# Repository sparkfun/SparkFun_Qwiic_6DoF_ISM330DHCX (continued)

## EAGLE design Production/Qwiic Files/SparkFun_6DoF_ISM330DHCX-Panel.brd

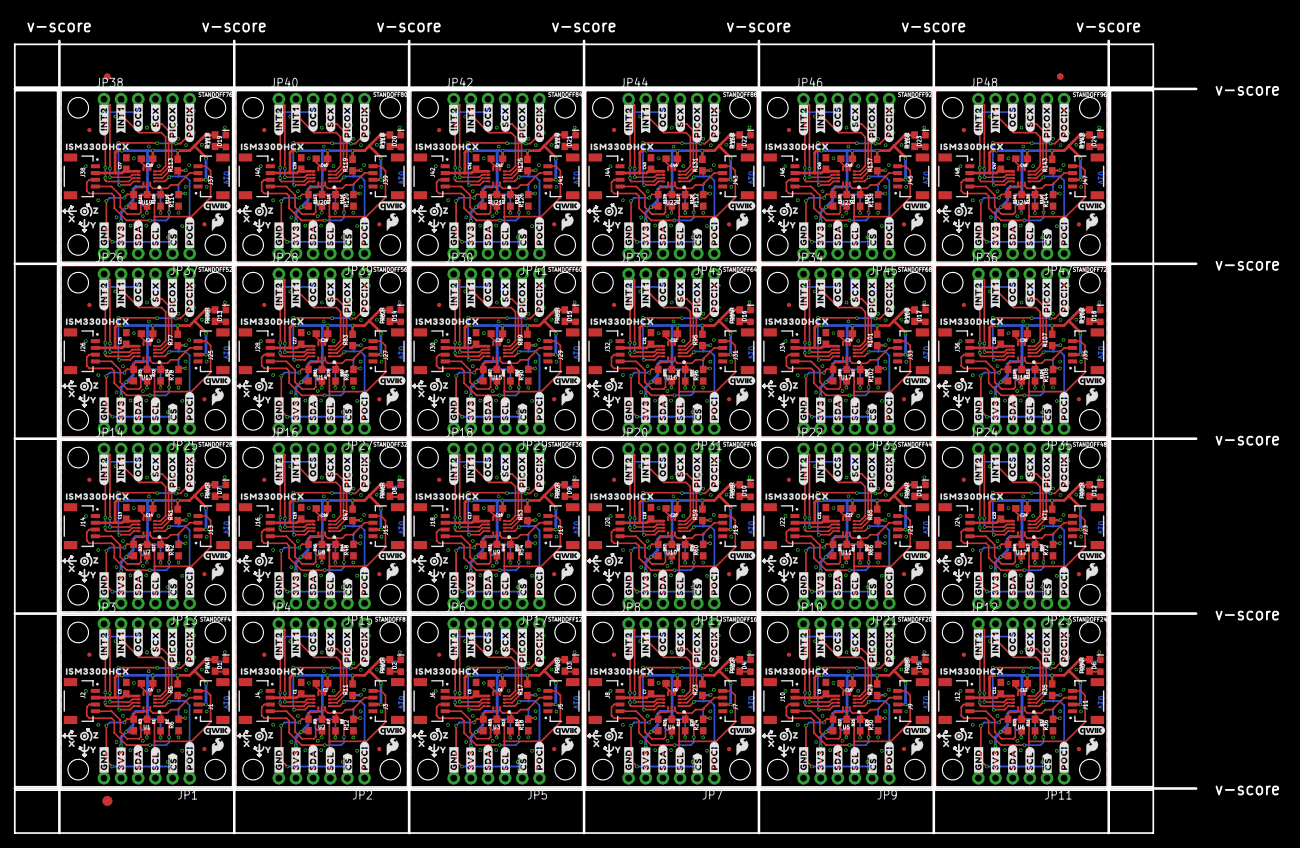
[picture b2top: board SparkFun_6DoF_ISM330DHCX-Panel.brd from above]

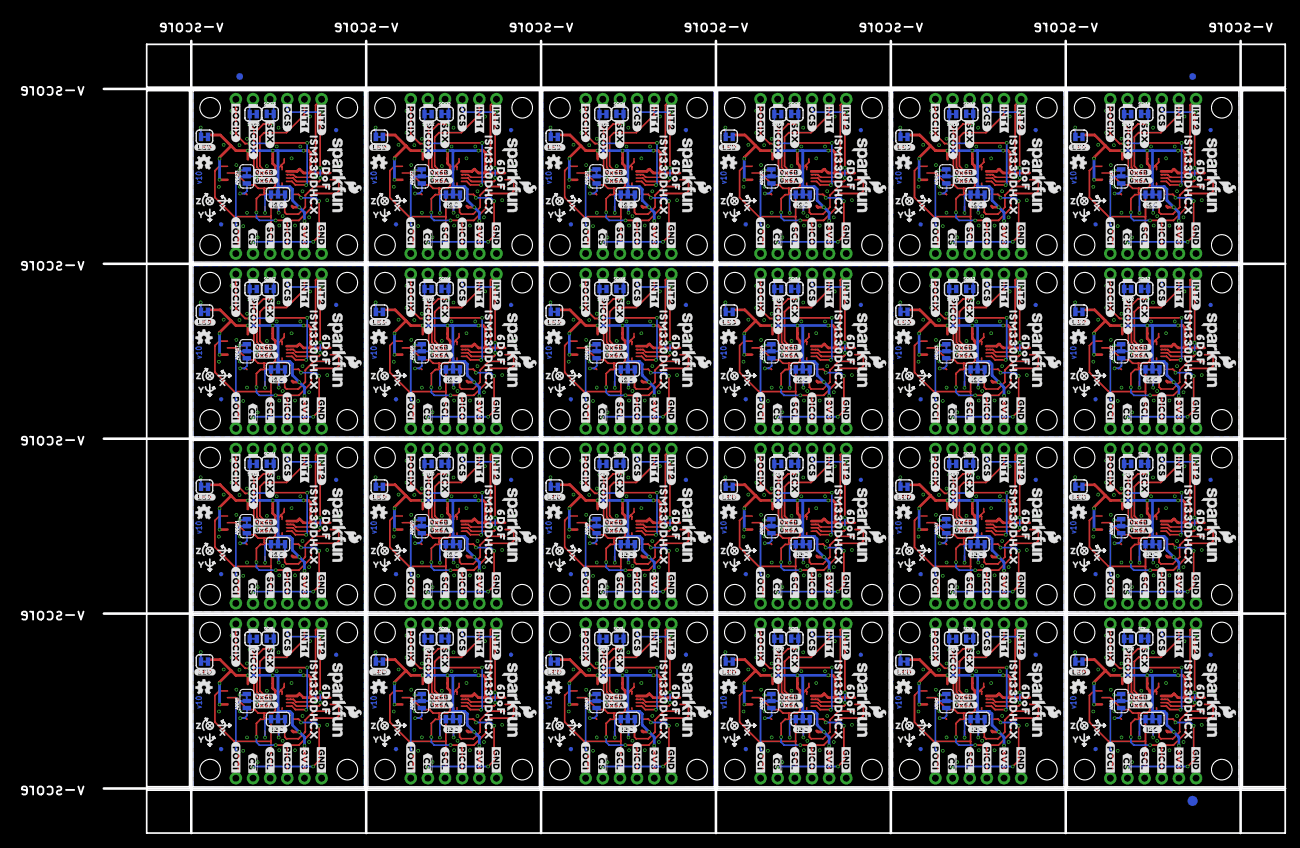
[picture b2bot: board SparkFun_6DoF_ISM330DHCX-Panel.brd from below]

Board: 2 copper layers, 175.0 x 117.3 mm, 1662 parts (723 on the bottom side), 432 nets.

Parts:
ADDR, ADDR1, ADDR2, ADDR3, ADDR4, ADDR5, ADDR6, ADDR7, ADDR8, ADDR9, ADDR10, ADDR11, ADDR12, ADDR13, ADDR14, ADDR15, ADDR16, ADDR17, ADDR18, ADDR19, ADDR20, ADDR21, ADDR22, ADDR23: JUMPER-SMT_3_1-NC_TRACE_SILK; SMT-JUMPER_3_1-NC_TRACE_SILK
C1, C2, C3, C4, C5, C6, C7, C8, C9, C10, C11, C12, C13, C14, C15, C16, C17, C18, C19, C20, C21, C22, C23, C24, C25, C26, C27, C28, C29, C30, C31, C32, C33, C34, C35, C36, C37, C38, C39, C40, C41, C42, C43, C44, C45, C46, C47, C48: 0.1uF; 0603
D1, D2, D3, D4, D5, D6, D7, D8, D9, D10, D11, D12, D13, D14, D15, D16, D17, D18, D19, D20, D21, D22, D23, D24: RED; LED-0603
E$1, E$2, E$3, E$4: FIDUCIAL-1X2
E$5, E$6: FIDUCIAL-1.5X3
FD1, FD2, FD3, FD4, FD5, FD6, FD7, FD8, FD9, FD10, FD11, FD12, FD13, FD14, FD15, FD16, FD17, FD18, FD19, FD20, FD21, FD22, FD23, FD24, FD25, FD26, FD27, FD28, FD29, FD30, FD31, FD32, FD33, FD34, FD35, FD36, FD37, FD38, FD39, FD40, FD41, FD42, FD43, FD44, FD45, FD46, FD47, FD48: FIDUCIALUFIDUCIAL; FIDUCIAL-MICRO
FID1, FID2, FID3, FID4, FID5, FID6, FID7, FID8, FID9, FID10, FID11, FID12, FID13, FID14, FID15, FID16, FID17, FID18, FID19, FID20, FID21, FID22, FID23, FID24, FID25, FID26, FID27, FID28, FID29, FID30, FID31, FID32, FID33, FID34, FID35, FID36, FID37, FID38, FID39, FID40, FID41, FID42, FID43, FID44, FID45, FID46, FID47, FID48: FIDUCIALUFIDUCIAL; FIDUCIAL-MICRO
I2C_PU, I2C_PU1, I2C_PU2, I2C_PU3, I2C_PU4, I2C_PU5, I2C_PU6, I2C_PU7, I2C_PU8, I2C_PU9, I2C_PU10, I2C_PU11, I2C_PU12, I2C_PU13, I2C_PU14, I2C_PU15, I2C_PU16, I2C_PU17, I2C_PU18, I2C_PU19, I2C_PU20, I2C_PU21, I2C_PU22, I2C_PU23: S_MODE; SMT-JUMPER_3_2-NC_TRACE_SILK
J1, J2, J3, J4, J5, J6, J7, J8, J9, J10, J11, J12, J13, J14, J15, J16, J17, J18, J19, J20, J21, J22, J23, J24, J25, J26, J27, J28, J29, J30, J31, J32, J33, J34, J35, J36, J37, J38, J39, J40, J41, J42, J43, J44, J45, J46, J47, J48: QWIIC_RIGHT_ANGLE; JST04_1MM_RA
JP1, JP2, JP3, JP4, JP5, JP6, JP7, JP8, JP9, JP10, JP11, JP12, JP13, JP14, JP15, JP16, JP17, JP18, JP19, JP20, JP21, JP22, JP23, JP24, JP25, JP26, JP27, JP28, JP29, JP30, JP31, JP32, JP33, JP34, JP35, JP36, JP37, JP38, JP39, JP40, JP41, JP42, JP43, JP44, JP45, JP46, JP47, JP48: IO; 1X06_NO_SILK
LED, LED1, LED2, LED3, LED4, LED5, LED6, LED7, LED8, LED9, LED10, LED11, LED12, LED13, LED14, LED15, LED16, LED17, LED18, LED19, LED20, LED21, LED22, LED23: JUMPER-SMT_2_NC_TRACE_SILK; SMT-JUMPER_2_NC_TRACE_SILK
LOGO1, LOGO6, LOGO9, LOGO12, LOGO15, LOGO18, LOGO21, LOGO24, LOGO27, LOGO30, LOGO33, LOGO36, LOGO39, LOGO42, LOGO45, LOGO48, LOGO51, LOGO54, LOGO57, LOGO60, LOGO63, LOGO66, LOGO69, LOGO72: QWIIC_LOGO_4MM; QWIIC_4MM
LOGO2, LOGO4, LOGO7, LOGO10, LOGO13, LOGO16, LOGO19, LOGO22, LOGO25, LOGO28, LOGO31, LOGO34, LOGO37, LOGO40, LOGO43, LOGO46, LOGO49, LOGO52, LOGO55, LOGO58, LOGO61, LOGO64, LOGO67, LOGO70: OSHW-LOGOMINI; OSHW-LOGO-MINI
LOGO3, LOGO5, LOGO8, LOGO11, LOGO14, LOGO17, LOGO20, LOGO23, LOGO26, LOGO29, LOGO32, LOGO35, LOGO38, LOGO41, LOGO44, LOGO47, LOGO50, LOGO53, LOGO56, LOGO59, LOGO62, LOGO65, LOGO68, LOGO71: SFE_LOGO_NAME_FLAME.1_INCH; SFE_LOGO_NAME_FLAME_.1
R1, R2, R7, R8, R13, R14, R19, R20, R25, R26, R31, R32, R37, R38, R43, R44, R49, R50, R55, R56, R61, R62, R67, R68, R73, R74, R79, R80, R85, R86, R91, R92, R97, R98, R103, R104, R109, R110, R115, R116, R121, R122, R127, R128, R133, R134, R139, R140: 2.2k; 0603
R3, R5, R6, R9, R11, R12, R15, R17, R18, R21, R23, R24, R27, R29, R30, R33, R35, R36, R39, R41, R42, R45, R47, R48, R51, R53, R54, R57, R59, R60, R63, R65, R66, R69, R71, R72, R75, R77, R78, R81, R83, R84, R87, R89, R90, R93, R95, R96, R99, R101, R102, R105, R107, R108, R111, R113, R114, R117, R119, R120, R123, R125, R126, R129, R131, R132, R135, R137, R138, R141, R143, R144: 10k; 0603
R4, R10, R16, R22, R28, R34, R40, R46, R52, R58, R64, R70, R76, R82, R88, R94, R100, R106, R112, R118, R124, R130, R136, R142: 1k; 0603
SCX, SCX1, SCX2, SCX3, SCX4, SCX5, SCX6, SCX7, SCX8, SCX9, SCX10, SCX11, SCX12, SCX13, SCX14, SCX15, SCX16, SCX17, SCX18, SCX19, SCX20, SCX21, SCX22, SCX23: JUMPER-SMT_2_NC_TRACE_SILK; SMT-JUMPER_2_NC_TRACE_SILK
SDX, SDX1, SDX2, SDX3, SDX4, SDX5, SDX6, SDX7, SDX8, SDX9, SDX10, SDX11, SDX12, SDX13, SDX14, SDX15, SDX16, SDX17, SDX18, SDX19, SDX20, SDX21, SDX22, SDX23: JUMPER-SMT_2_NC_TRACE_SILK; SMT-JUMPER_2_NC_TRACE_SILK
STANDOFF1, STANDOFF2, STANDOFF3, STANDOFF4, STANDOFF5, STANDOFF6, STANDOFF7, STANDOFF8, STANDOFF9, STANDOFF10, STANDOFF11, STANDOFF12, STANDOFF13, STANDOFF14, STANDOFF15, STANDOFF16, STANDOFF17, STANDOFF18, STANDOFF19, STANDOFF20, STANDOFF21, STANDOFF22, STANDOFF23, STANDOFF24, STANDOFF25, STANDOFF26, STANDOFF27, STANDOFF28, STANDOFF29, STANDOFF30, STANDOFF31, STANDOFF32, STANDOFF33, STANDOFF34, STANDOFF35, STANDOFF36, STANDOFF37, STANDOFF38, STANDOFF39, STANDOFF40, STANDOFF41, STANDOFF42, STANDOFF43, STANDOFF44, STANDOFF45, STANDOFF46, STANDOFF47, STANDOFF48, STANDOFF49, STANDOFF50, STANDOFF51, STANDOFF52, STANDOFF53, STANDOFF54, STANDOFF55, STANDOFF56, STANDOFF57, STANDOFF58, STANDOFF59, STANDOFF60, STANDOFF61, STANDOFF62, STANDOFF63, STANDOFF64, STANDOFF65, STANDOFF66, STANDOFF67, STANDOFF68, STANDOFF69, STANDOFF70, STANDOFF71, STANDOFF72, STANDOFF73, STANDOFF74, STANDOFF75, STANDOFF76, STANDOFF77, STANDOFF78, STANDOFF79, STANDOFF80, STANDOFF81, STANDOFF82, STANDOFF83, STANDOFF84, STANDOFF85, STANDOFF86, STANDOFF87, STANDOFF88, STANDOFF89, STANDOFF90, STANDOFF91, STANDOFF92, STANDOFF93, STANDOFF94, STANDOFF95, STANDOFF96: STAND-OFFTIGHT; STAND-OFF-TIGHT
U1, U2, U3, U4, U5, U6, U7, U8, U9, U10, U11, U12, U13, U14, U15, U16, U17, U18, U19, U20, U21, U22, U23, U24: ISM330DHCX; LGA-14L
U$1, U$15, U$21, U$46, U$79, U$85, U$118, U$124, U$157, U$163, U$196, U$202, U$235, U$241, U$274, U$280, U$313, U$319, U$352, U$358, U$391, U$397, U$430, U$436, U$469, U$475, U$508, U$514, U$547, U$553, U$586, U$592, U$625, U$631, U$664, U$670, U$703, U$709, U$742, U$748, U$781, U$787, U$820, U$826, U$859, U$865, U$898, U$904: #3V3#1
U$2, U$17, U$41, U$47, U$80, U$86, U$119, U$125, U$158, U$164, U$197, U$203, U$236, U$242, U$275, U$281, U$314, U$320, U$353, U$359, U$392, U$398, U$431, U$437, U$470, U$476, U$509, U$515, U$548, U$554, U$587, U$593, U$626, U$632, U$665, U$671, U$704, U$710, U$743, U$749, U$782, U$788, U$821, U$827, U$860, U$866, U$899, U$905: #GND#0
U$3, U$58, U$97, U$136, U$175, U$214, U$253, U$292, U$331, U$370, U$409, U$448, U$487, U$526, U$565, U$604, U$643, U$682, U$721, U$760, U$799, U$838, U$877, U$916: ##CS##7
U$4, U$42, U$81, U$120, U$159, U$198, U$237, U$276, U$315, U$354, U$393, U$432, U$471, U$510, U$549, U$588, U$627, U$666, U$705, U$744, U$783, U$822, U$861, U$900: #SDA#4
U$5, U$22, U$43, U$49, U$82, U$88, U$121, U$127, U$160, U$166, U$199, U$205, U$238, U$244, U$277, U$283, U$316, U$322, U$355, U$361, U$394, U$400, U$433, U$439, U$472, U$478, U$511, U$517, U$550, U$556, U$589, U$595, U$628, U$634, U$667, U$673, U$706, U$712, U$745, U$751, U$784, U$790, U$823, U$829, U$862, U$868, U$901, U$907: #SCL#5
U$6, U$69, U$108, U$147, U$186, U$225, U$264, U$303, U$342, U$381, U$420, U$459, U$498, U$537, U$576, U$615, U$654, U$693, U$732, U$771, U$810, U$849, U$888, U$927: #POCI#11
U$7, U$19, U$56, U$57, U$95, U$96, U$134, U$135, U$173, U$174, U$212, U$213, U$251, U$252, U$290, U$291, U$329, U$330, U$368, U$369, U$407, U$408, U$446, U$447, U$485, U$486, U$524, U$525, U$563, U$564, U$602, U$603, U$641, U$642, U$680, U$681, U$719, U$720, U$758, U$759, U$797, U$798, U$836, U$837, U$875, U$876, U$914, U$915: #INT1#9
U$8, U$78, U$117, U$156, U$195, U$234, U$273, U$312, U$351, U$390, U$429, U$468, U$507, U$546, U$585, U$624, U$663, U$702, U$741, U$780, U$819, U$858, U$897, U$936: #INT2#2
U$9, U$44, U$83, U$122, U$161, U$200, U$239, U$278, U$317, U$356, U$395, U$434, U$473, U$512, U$551, U$590, U$629, U$668, U$707, U$746, U$785, U$824, U$863, U$902: #OCS#8
U$10, U$45, U$84, U$123, U$162, U$201, U$240, U$279, U$318, U$357, U$396, U$435, U$474, U$513, U$552, U$591, U$630, U$669, U$708, U$747, U$786, U$825, U$864, U$903: #SCX#9
U$11, U$64, U$103, U$142, U$181, U$220, U$259, U$298, U$337, U$376, U$415, U$454, U$493, U$532, U$571, U$610, U$649, U$688, U$727, U$766, U$805, U$844, U$883, U$922: #PICOX#10
U$12, U$62, U$101, U$140, U$179, U$218, U$257, U$296, U$335, U$374, U$413, U$452, U$491, U$530, U$569, U$608, U$647, U$686, U$725, U$764, U$803, U$842, U$881, U$920: ISM330DHCX331
U$13, U$52, U$91, U$130, U$169, U$208, U$247, U$286, U$325, U$364, U$403, U$442, U$481, U$520, U$559, U$598, U$637, U$676, U$715, U$754, U$793, U$832, U$871, U$910: #0X6A#11
U$14, U$53, U$92, U$131, U$170, U$209, U$248, U$287, U$326, U$365, U$404, U$443, U$482, U$521, U$560, U$599, U$638, U$677, U$716, U$755, U$794, U$833, U$872, U$911: #0X6B#11
U$16, U$51, U$90, U$129, U$168, U$207, U$246, U$285, U$324, U$363, U$402, U$441, U$480, U$519, U$558, U$597, U$636, U$675, U$714, U$753, U$792, U$831, U$870, U$909: #LED#11
U$18, U$70, U$109, U$148, U$187, U$226, U$265, U$304, U$343, U$382, U$421, U$460, U$499, U$538, U$577, U$616, U$655, U$694, U$733, U$772, U$811, U$850, U$889, U$928: #POCI#12
U$20, U$48, U$87, U$126, U$165, U$204, U$243, U$282, U$321, U$360, U$399, U$438, U$477, U$516, U$555, U$594, U$633, U$672, U$711, U$750, U$789, U$828, U$867, U$906: #OCS#7
U$23, U$50, U$89, U$128, U$167, U$206, U$245, U$284, U$323, U$362, U$401, U$440, U$479, U$518, U$557, U$596, U$635, U$674, U$713, U$752, U$791, U$830, U$869, U$908: #SCX#8
U$24, U$65, U$104, U$143, U$182, U$221, U$260, U$299, U$338, U$377, U$416, U$455, U$494, U$533, U$572, U$611, U$650, U$689, U$728, U$767, U$806, U$845, U$884, U$923: #POCIX#8
U$25, U$54, U$93, U$132, U$171, U$210, U$249, U$288, U$327, U$366, U$405, U$444, U$483, U$522, U$561, U$600, U$639, U$678, U$717, U$756, U$795, U$834, U$873, U$912: #I2C#11
U$26, U$68, U$107, U$146, U$185, U$224, U$263, U$302, U$341, U$380, U$419, U$458, U$497, U$536, U$575, U$614, U$653, U$692, U$731, U$770, U$809, U$848, U$887, U$926: #PICO#13
U$27, U$59, U$98, U$137, U$176, U$215, U$254, U$293, U$332, U$371, U$410, U$449, U$488, U$527, U$566, U$605, U$644, U$683, U$722, U$761, U$800, U$839, U$878, U$917: ##CS##8
U$28, U$55, U$94, U$133, U$172, U$211, U$250, U$289, U$328, U$367, U$406, U$445, U$484, U$523, U$562, U$601, U$640, U$679, U$718, U$757, U$796, U$835, U$874, U$913: PWR8
U$29, U$61, U$100, U$139, U$178, U$217, U$256, U$295, U$334, U$373, U$412, U$451, U$490, U$529, U$568, U$607, U$646, U$685, U$724, U$763, U$802, U$841, U$880, U$919: SFE_LOGO_FLAME_.1
U$30, U$63, U$102, U$141, U$180, U$219, U$258, U$297, U$336, U$375, U$414, U$453, U$492, U$531, U$570, U$609, U$648, U$687, U$726, U$765, U$804, U$843, U$882, U$921: ISM330DHCX20
U$31, U$60, U$99, U$138, U$177, U$216, U$255, U$294, U$333, U$372, U$411, U$450, U$489, U$528, U$567, U$606, U$645, U$684, U$723, U$762, U$801, U$840, U$879, U$918: 6DOF12
U$32, U$66, U$105, U$144, U$183, U$222, U$261, U$300, U$339, U$378, U$417, U$456, U$495, U$534, U$573, U$612, U$651, U$690, U$729, U$768, U$807, U$846, U$885, U$924: #PICOX#9
U$33, U$67, U$106, U$145, U$184, U$223, U$262, U$301, U$340, U$379, U$418, U$457, U$496, U$535, U$574, U$613, U$652, U$691, U$730, U$769, U$808, U$847, U$886, U$925: #POCIX#7
U$34, U$37, U$71, U$74, U$110, U$113, U$149, U$152, U$188, U$191, U$227, U$230, U$266, U$269, U$305, U$308, U$344, U$347, U$383, U$386, U$422, U$425, U$461, U$464, U$500, U$503, U$539, U$542, U$578, U$581, U$617, U$620, U$656, U$659, U$695, U$698, U$734, U$737, U$773, U$776, U$812, U$815, U$851, U$854, U$890, U$893, U$929, U$932: X2114
U$35, U$38, U$72, U$75, U$111, U$114, U$150, U$153, U$189, U$192, U$228, U$231, U$267, U$270, U$306, U$309, U$345, U$348, U$384, U$387, U$423, U$426, U$462, U$465, U$501, U$504, U$540, U$543, U$579, U$582, U$618, U$621, U$657, U$660, U$696, U$699, U$735, U$738, U$774, U$777, U$813, U$816, U$852, U$855, U$891, U$894, U$930, U$933: Y2115
U$36, U$39, U$73, U$76, U$112, U$115, U$151, U$154, U$190, U$193, U$229, U$232, U$268, U$271, U$307, U$310, U$346, U$349, U$385, U$388, U$424, U$427, U$463, U$466, U$502, U$505, U$541, U$544, U$580, U$583, U$619, U$622, U$658, U$661, U$697, U$700, U$736, U$739, U$775, U$778, U$814, U$817, U$853, U$856, U$892, U$895, U$931, U$934: Z2116
U$40, U$77, U$116, U$155, U$194, U$233, U$272, U$311, U$350, U$389, U$428, U$467, U$506, U$545, U$584, U$623, U$662, U$701, U$740, U$779, U$818, U$857, U$896, U$935: #INT2#3

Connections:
3.3V: C3.1, C4.1, I2C_PU.2, J1.2, J2.2, JP1.5, R3.2, R4.2, R5.2, U1.P5, U1.P8
3.3V1: C1.1, C2.1, I2C_PU1.2, J3.2, J4.2, JP2.5, R9.2, R10.2, R11.2, U2.P5, U2.P8
3.3V2: C5.1, C6.1, I2C_PU2.2, J5.2, J6.2, JP5.5, R15.2, R16.2, R17.2, U3.P5, U3.P8
3.3V3: C7.1, C8.1, I2C_PU3.2, J7.2, J8.2, JP7.5, R21.2, R22.2, R23.2, U4.P5, U4.P8
3.3V4: C9.1, C10.1, I2C_PU4.2, J9.2, J10.2, JP9.5, R27.2, R28.2, R29.2, U5.P5, U5.P8
3.3V5: C11.1, C12.1, I2C_PU5.2, J11.2, J12.2, JP11.5, R33.2, R34.2, R35.2, U6.P5, U6.P8
3.3V6: C13.1, C14.1, I2C_PU6.2, J13.2, J14.2, JP13.5, R39.2, R40.2, R41.2, U7.P5, U7.P8
3.3V7: C15.1, C16.1, I2C_PU7.2, J15.2, J16.2, JP15.5, R45.2, R46.2, R47.2, U8.P5, U8.P8
3.3V8: C17.1, C18.1, I2C_PU8.2, J17.2, J18.2, JP17.5, R51.2, R52.2, R53.2, U9.P5, U9.P8
3.3V9: C19.1, C20.1, I2C_PU9.2, J19.2, J20.2, JP19.5, R57.2, R58.2, R59.2, U10.P5, U10.P8
3.3V10: C21.1, C22.1, I2C_PU10.2, J21.2, J22.2, JP21.5, R63.2, R64.2, R65.2, U11.P5, U11.P8
3.3V11: C23.1, C24.1, I2C_PU11.2, J23.2, J24.2, JP23.5, R69.2, R70.2, R71.2, U12.P5, U12.P8
3.3V12: C25.1, C26.1, I2C_PU12.2, J25.2, J26.2, JP25.5, R75.2, R76.2, R77.2, U13.P5, U13.P8
3.3V13: C27.1, C28.1, I2C_PU13.2, J27.2, J28.2, JP27.5, R81.2, R82.2, R83.2, U14.P5, U14.P8
3.3V14: C29.1, C30.1, I2C_PU14.2, J29.2, J30.2, JP29.5, R87.2, R88.2, R89.2, U15.P5, U15.P8
3.3V15: C31.1, C32.1, I2C_PU15.2, J31.2, J32.2, JP31.5, R93.2, R94.2, R95.2, U16.P5, U16.P8
3.3V16: C33.1, C34.1, I2C_PU16.2, J33.2, J34.2, JP33.5, R99.2, R100.2, R101.2, U17.P5, U17.P8
3.3V17: C35.1, C36.1, I2C_PU17.2, J35.2, J36.2, JP35.5, R105.2, R106.2, R107.2, U18.P5, U18.P8
3.3V18: C37.1, C38.1, I2C_PU18.2, J37.2, J38.2, JP37.5, R111.2, R112.2, R113.2, U19.P5, U19.P8
3.3V19: C39.1, C40.1, I2C_PU19.2, J39.2, J40.2, JP39.5, R117.2, R118.2, R119.2, U20.P5, U20.P8
3.3V20: C41.1, C42.1, I2C_PU20.2, J41.2, J42.2, JP41.5, R123.2, R124.2, R125.2, U21.P5, U21.P8
3.3V21: C43.1, C44.1, I2C_PU21.2, J43.2, J44.2, JP43.5, R129.2, R130.2, R131.2, U22.P5, U22.P8
3.3V22: C45.1, C46.1, I2C_PU22.2, J45.2, J46.2, JP45.5, R135.2, R136.2, R137.2, U23.P5, U23.P8
3.3V23: C47.1, C48.1, I2C_PU23.2, J47.2, J48.2, JP47.5, R141.2, R142.2, R143.2, U24.P5, U24.P8
!CS!: JP1.2, R3.1, U1.P12
!CS!1: JP2.2, R9.1, U2.P12
!CS!2: JP5.2, R15.1, U3.P12
!CS!3: JP7.2, R21.1, U4.P12
!CS!4: JP9.2, R27.1, U5.P12
!CS!5: JP11.2, R33.1, U6.P12
!CS!6: JP13.2, R39.1, U7.P12
!CS!7: JP15.2, R45.1, U8.P12
!CS!8: JP17.2, R51.1, U9.P12
!CS!9: JP19.2, R57.1, U10.P12
!CS!10: JP21.2, R63.1, U11.P12
!CS!11: JP23.2, R69.1, U12.P12
!CS!12: JP25.2, R75.1, U13.P12
!CS!13: JP27.2, R81.1, U14.P12
!CS!14: JP29.2, R87.1, U15.P12
!CS!15: JP31.2, R93.1, U16.P12
!CS!16: JP33.2, R99.1, U17.P12
!CS!17: JP35.2, R105.1, U18.P12
!CS!18: JP37.2, R111.1, U19.P12
!CS!19: JP39.2, R117.1, U20.P12
!CS!20: JP41.2, R123.1, U21.P12
!CS!21: JP43.2, R129.1, U22.P12
!CS!22: JP45.2, R135.1, U23.P12
!CS!23: JP47.2, R141.1, U24.P12
GND: C3.2, C4.2, J1.1, J2.1, JP1.6, LED.1, R6.1, SCX.1, SDX.1, U1.P6, U1.P7
GND1: C1.2, C2.2, J3.1, J4.1, JP2.6, LED1.1, R12.1, SCX1.1, SDX1.1, U2.P6, U2.P7
GND2: C5.2, C6.2, J5.1, J6.1, JP5.6, LED2.1, R18.1, SCX2.1, SDX2.1, U3.P6, U3.P7
GND3: C7.2, C8.2, J7.1, J8.1, JP7.6, LED3.1, R24.1, SCX3.1, SDX3.1, U4.P6, U4.P7
GND4: C9.2, C10.2, J9.1, J10.1, JP9.6, LED4.1, R30.1, SCX4.1, SDX4.1, U5.P6, U5.P7
GND5: C11.2, C12.2, J11.1, J12.1, JP11.6, LED5.1, R36.1, SCX5.1, SDX5.1, U6.P6, U6.P7
GND6: C13.2, C14.2, J13.1, J14.1, JP13.6, LED6.1, R42.1, SCX6.1, SDX6.1, U7.P6, U7.P7
GND7: C15.2, C16.2, J15.1, J16.1, JP15.6, LED7.1, R48.1, SCX7.1, SDX7.1, U8.P6, U8.P7
GND8: C17.2, C18.2, J17.1, J18.1, JP17.6, LED8.1, R54.1, SCX8.1, SDX8.1, U9.P6, U9.P7
GND9: C19.2, C20.2, J19.1, J20.1, JP19.6, LED9.1, R60.1, SCX9.1, SDX9.1, U10.P6, U10.P7
GND10: C21.2, C22.2, J21.1, J22.1, JP21.6, LED10.1, R66.1, SCX10.1, SDX10.1, U11.P6, U11.P7
GND11: C23.2, C24.2, J23.1, J24.1, JP23.6, LED11.1, R72.1, SCX11.1, SDX11.1, U12.P6, U12.P7
GND12: C25.2, C26.2, J25.1, J26.1, JP25.6, LED12.1, R78.1, SCX12.1, SDX12.1, U13.P6, U13.P7
GND13: C27.2, C28.2, J27.1, J28.1, JP27.6, LED13.1, R84.1, SCX13.1, SDX13.1, U14.P6, U14.P7
GND14: C29.2, C30.2, J29.1, J30.1, JP29.6, LED14.1, R90.1, SCX14.1, SDX14.1, U15.P6, U15.P7
GND15: C31.2, C32.2, J31.1, J32.1, JP31.6, LED15.1, R96.1, SCX15.1, SDX15.1, U16.P6, U16.P7
GND16: C33.2, C34.2, J33.1, J34.1, JP33.6, LED16.1, R102.1, SCX16.1, SDX16.1, U17.P6, U17.P7
GND17: C35.2, C36.2, J35.1, J36.1, JP35.6, LED17.1, R108.1, SCX17.1, SDX17.1, U18.P6, U18.P7
GND18: C37.2, C38.2, J37.1, J38.1, JP37.6, LED18.1, R114.1, SCX18.1, SDX18.1, U19.P6, U19.P7
GND19: C39.2, C40.2, J39.1, J40.1, JP39.6, LED19.1, R120.1, SCX19.1, SDX19.1, U20.P6, U20.P7
GND20: C41.2, C42.2, J41.1, J42.1, JP41.6, LED20.1, R126.1, SCX20.1, SDX20.1, U21.P6, U21.P7
GND21: C43.2, C44.2, J43.1, J44.1, JP43.6, LED21.1, R132.1, SCX21.1, SDX21.1, U22.P6, U22.P7
GND22: C45.2, C46.2, J45.1, J46.1, JP45.6, LED22.1, R138.1, SCX22.1, SDX22.1, U23.P6, U23.P7
GND23: C47.2, C48.2, J47.1, J48.1, JP47.6, LED23.1, R144.1, SCX23.1, SDX23.1, U24.P6, U24.P7
INT1: JP3.2, U1.P4
INT2: JP3.1, U1.P9
INT3: JP4.2, U2.P4
INT4: JP4.1, U2.P9
INT5: JP6.2, U3.P4
INT6: JP6.1, U3.P9
INT7: JP8.2, U4.P4
INT8: JP8.1, U4.P9
INT9: JP10.2, U5.P4
INT10: JP10.1, U5.P9
INT11: JP12.2, U6.P4
INT12: JP12.1, U6.P9
INT13: JP14.2, U7.P4
INT14: JP14.1, U7.P9
INT15: JP16.2, U8.P4
INT16: JP16.1, U8.P9
INT17: JP18.2, U9.P4
INT18: JP18.1, U9.P9
INT19: JP20.2, U10.P4
INT20: JP20.1, U10.P9
INT21: JP22.2, U11.P4
INT22: JP22.1, U11.P9
INT23: JP24.2, U12.P4
INT24: JP24.1, U12.P9
INT25: JP26.2, U13.P4
INT26: JP26.1, U13.P9
INT27: JP28.2, U14.P4
INT28: JP28.1, U14.P9
INT29: JP30.2, U15.P4
INT30: JP30.1, U15.P9
INT31: JP32.2, U16.P4
INT32: JP32.1, U16.P9
INT33: JP34.2, U17.P4
INT34: JP34.1, U17.P9
INT35: JP36.2, U18.P4
INT36: JP36.1, U18.P9
INT37: JP38.2, U19.P4
INT38: JP38.1, U19.P9
INT39: JP40.2, U20.P4
INT40: JP40.1, U20.P9
INT41: JP42.2, U21.P4
INT42: JP42.1, U21.P9
INT43: JP44.2, U22.P4
INT44: JP44.1, U22.P9
INT45: JP46.2, U23.P4
INT46: JP46.1, U23.P9
INT47: JP48.2, U24.P4
INT48: JP48.1, U24.P9
unnamed: ADDR.3, R5.1
unnamed: D1.A, R4.1
unnamed: D1.C, LED.2
unnamed: I2C_PU1.1, R7.2
unnamed: I2C_PU.1, R1.2
unnamed: I2C_PU.3, R2.2
unnamed: ADDR.1, R6.2
unnamed: I2C_PU1.3, R8.2
unnamed: D2.A, R10.1
unnamed: D2.C, LED1.2
unnamed: ADDR1.3, R11.1
unnamed: ADDR1.1, R12.2
unnamed: I2C_PU2.1, R13.2
unnamed: I2C_PU2.3, R14.2
unnamed: D3.A, R16.1
unnamed: D3.C, LED2.2
unnamed: ADDR2.3, R17.1
unnamed: ADDR2.1, R18.2
unnamed: I2C_PU3.1, R19.2
unnamed: I2C_PU3.3, R20.2
unnamed: D4.A, R22.1
unnamed: D4.C, LED3.2
unnamed: ADDR3.3, R23.1
unnamed: ADDR3.1, R24.2
unnamed: I2C_PU4.1, R25.2
unnamed: I2C_PU4.3, R26.2
unnamed: D5.A, R28.1
unnamed: D5.C, LED4.2
unnamed: ADDR4.3, R29.1
unnamed: ADDR4.1, R30.2
unnamed: I2C_PU5.1, R31.2
unnamed: I2C_PU5.3, R32.2
unnamed: D6.A, R34.1
unnamed: D6.C, LED5.2
unnamed: ADDR5.3, R35.1
unnamed: ADDR5.1, R36.2
unnamed: I2C_PU6.1, R37.2
unnamed: I2C_PU6.3, R38.2
unnamed: D7.A, R40.1
unnamed: D7.C, LED6.2
unnamed: ADDR6.3, R41.1
unnamed: ADDR6.1, R42.2
unnamed: I2C_PU7.1, R43.2
unnamed: I2C_PU7.3, R44.2
unnamed: D8.A, R46.1
unnamed: D8.C, LED7.2
unnamed: ADDR7.3, R47.1
unnamed: ADDR7.1, R48.2
unnamed: I2C_PU8.1, R49.2
unnamed: I2C_PU8.3, R50.2
unnamed: D9.A, R52.1
unnamed: D9.C, LED8.2
unnamed: ADDR8.3, R53.1
unnamed: ADDR8.1, R54.2
unnamed: I2C_PU9.1, R55.2
unnamed: I2C_PU9.3, R56.2
unnamed: D10.A, R58.1
unnamed: D10.C, LED9.2
unnamed: ADDR9.3, R59.1
unnamed: ADDR9.1, R60.2
unnamed: I2C_PU10.1, R61.2
unnamed: I2C_PU10.3, R62.2
unnamed: D11.A, R64.1
unnamed: D11.C, LED10.2
unnamed: ADDR10.3, R65.1
unnamed: ADDR10.1, R66.2
unnamed: I2C_PU11.1, R67.2
unnamed: I2C_PU11.3, R68.2
unnamed: D12.A, R70.1
unnamed: D12.C, LED11.2
unnamed: ADDR11.3, R71.1
unnamed: ADDR11.1, R72.2
unnamed: I2C_PU12.1, R73.2
unnamed: I2C_PU12.3, R74.2
unnamed: D13.A, R76.1
unnamed: D13.C, LED12.2
unnamed: ADDR12.3, R77.1
unnamed: ADDR12.1, R78.2
unnamed: I2C_PU13.1, R79.2
unnamed: I2C_PU13.3, R80.2
unnamed: D14.A, R82.1
unnamed: D14.C, LED13.2
unnamed: ADDR13.3, R83.1
unnamed: ADDR13.1, R84.2
unnamed: I2C_PU14.1, R85.2
unnamed: I2C_PU14.3, R86.2
unnamed: D15.A, R88.1
unnamed: D15.C, LED14.2
unnamed: ADDR14.3, R89.1
unnamed: ADDR14.1, R90.2
unnamed: I2C_PU15.1, R91.2
unnamed: I2C_PU15.3, R92.2
unnamed: D16.A, R94.1
unnamed: D16.C, LED15.2
unnamed: ADDR15.3, R95.1
unnamed: ADDR15.1, R96.2
unnamed: I2C_PU16.1, R97.2
unnamed: I2C_PU16.3, R98.2
unnamed: D17.A, R100.1
unnamed: D17.C, LED16.2
unnamed: ADDR16.3, R101.1
unnamed: ADDR16.1, R102.2
unnamed: I2C_PU17.1, R103.2
unnamed: I2C_PU17.3, R104.2
unnamed: D18.A, R106.1
unnamed: D18.C, LED17.2
unnamed: ADDR17.3, R107.1
unnamed: ADDR17.1, R108.2
unnamed: I2C_PU18.1, R109.2
unnamed: I2C_PU18.3, R110.2
unnamed: D19.A, R112.1
unnamed: D19.C, LED18.2
unnamed: ADDR18.3, R113.1
unnamed: ADDR18.1, R114.2
unnamed: I2C_PU19.1, R115.2
unnamed: I2C_PU19.3, R116.2
unnamed: D20.A, R118.1
unnamed: D20.C, LED19.2
unnamed: ADDR19.3, R119.1
unnamed: ADDR19.1, R120.2
unnamed: I2C_PU20.1, R121.2
unnamed: I2C_PU20.3, R122.2
unnamed: D21.A, R124.1
unnamed: D21.C, LED20.2
unnamed: ADDR20.3, R125.1
unnamed: ADDR20.1, R126.2
unnamed: I2C_PU21.1, R127.2
unnamed: I2C_PU21.3, R128.2
unnamed: D22.A, R130.1
unnamed: D22.C, LED21.2
unnamed: ADDR21.3, R131.1
unnamed: ADDR21.1, R132.2
unnamed: I2C_PU22.1, R133.2
unnamed: I2C_PU22.3, R134.2
unnamed: D23.A, R136.1
unnamed: D23.C, LED22.2
unnamed: ADDR22.3, R137.1
unnamed: ADDR22.1, R138.2
unnamed: I2C_PU23.1, R139.2
unnamed: I2C_PU23.3, R140.2
unnamed: D24.A, R142.1
unnamed: D24.C, LED23.2
unnamed: ADDR23.3, R143.1
unnamed: ADDR23.1, R144.2
OCS: JP3.3, U1.P10
OCS1: JP4.3, U2.P10
OCS2: JP6.3, U3.P10
OCS3: JP8.3, U4.P10
OCS4: JP10.3, U5.P10
OCS5: JP12.3, U6.P10
OCS6: JP14.3, U7.P10
OCS7: JP16.3, U8.P10
OCS8: JP18.3, U9.P10
OCS9: JP20.3, U10.P10
OCS10: JP22.3, U11.P10
OCS11: JP24.3, U12.P10
OCS12: JP26.3, U13.P10
OCS13: JP28.3, U14.P10
OCS14: JP30.3, U15.P10
OCS15: JP32.3, U16.P10
OCS16: JP34.3, U17.P10
OCS17: JP36.3, U18.P10
OCS18: JP38.3, U19.P10
OCS19: JP40.3, U20.P10
OCS20: JP42.3, U21.P10
OCS21: JP44.3, U22.P10
OCS22: JP46.3, U23.P10
OCS23: JP48.3, U24.P10
PICO_AUX: JP3.5, SDX.2, U1.P2
PICO_AUX1: JP4.5, SDX1.2, U2.P2
PICO_AUX2: JP6.5, SDX2.2, U3.P2
PICO_AUX3: JP8.5, SDX3.2, U4.P2
PICO_AUX4: JP10.5, SDX4.2, U5.P2
PICO_AUX5: JP12.5, SDX5.2, U6.P2
PICO_AUX6: JP14.5, SDX6.2, U7.P2
PICO_AUX7: JP16.5, SDX7.2, U8.P2
PICO_AUX8: JP18.5, SDX8.2, U9.P2
PICO_AUX9: JP20.5, SDX9.2, U10.P2
PICO_AUX10: JP22.5, SDX10.2, U11.P2
PICO_AUX11: JP24.5, SDX11.2, U12.P2
PICO_AUX12: JP26.5, SDX12.2, U13.P2
PICO_AUX13: JP28.5, SDX13.2, U14.P2
PICO_AUX14: JP30.5, SDX14.2, U15.P2
PICO_AUX15: JP32.5, SDX15.2, U16.P2
PICO_AUX16: JP34.5, SDX16.2, U17.P2
PICO_AUX17: JP36.5, SDX17.2, U18.P2
PICO_AUX18: JP38.5, SDX18.2, U19.P2
PICO_AUX19: JP40.5, SDX19.2, U20.P2
PICO_AUX20: JP42.5, SDX20.2, U21.P2
PICO_AUX21: JP44.5, SDX21.2, U22.P2
PICO_AUX22: JP46.5, SDX22.2, U23.P2
PICO_AUX23: JP48.5, SDX23.2, U24.P2
POCI/SA0: ADDR.2, JP1.1, U1.P1
POCI/SA1: ADDR1.2, JP2.1, U2.P1
POCI/SA2: ADDR2.2, JP5.1, U3.P1
POCI/SA3: ADDR3.2, JP7.1, U4.P1
POCI/SA4: ADDR4.2, JP9.1, U5.P1
POCI/SA5: ADDR5.2, JP11.1, U6.P1
POCI/SA6: ADDR6.2, JP13.1, U7.P1
POCI/SA7: ADDR7.2, JP15.1, U8.P1
POCI/SA8: ADDR8.2, JP17.1, U9.P1
POCI/SA9: ADDR9.2, JP19.1, U10.P1
POCI/SA10: ADDR10.2, JP21.1, U11.P1
POCI/SA11: ADDR11.2, JP23.1, U12.P1
POCI/SA12: ADDR12.2, JP25.1, U13.P1
POCI/SA13: ADDR13.2, JP27.1, U14.P1
POCI/SA14: ADDR14.2, JP29.1, U15.P1
POCI/SA15: ADDR15.2, JP31.1, U16.P1
POCI/SA16: ADDR16.2, JP33.1, U17.P1
POCI/SA17: ADDR17.2, JP35.1, U18.P1
POCI/SA18: ADDR18.2, JP37.1, U19.P1
POCI/SA19: ADDR19.2, JP39.1, U20.P1
POCI/SA20: ADDR20.2, JP41.1, U21.P1
POCI/SA21: ADDR21.2, JP43.1, U22.P1
POCI/SA22: ADDR22.2, JP45.1, U23.P1
POCI/SA23: ADDR23.2, JP47.1, U24.P1
POCI_AUX: JP3.6, U1.P11
POCI_AUX1: JP4.6, U2.P11
POCI_AUX2: JP6.6, U3.P11
POCI_AUX3: JP8.6, U4.P11
POCI_AUX4: JP10.6, U5.P11
POCI_AUX5: JP12.6, U6.P11
POCI_AUX6: JP14.6, U7.P11
POCI_AUX7: JP16.6, U8.P11
POCI_AUX8: JP18.6, U9.P11
POCI_AUX9: JP20.6, U10.P11
POCI_AUX10: JP22.6, U11.P11
POCI_AUX11: JP24.6, U12.P11
POCI_AUX12: JP26.6, U13.P11
POCI_AUX13: JP28.6, U14.P11
POCI_AUX14: JP30.6, U15.P11
POCI_AUX15: JP32.6, U16.P11
POCI_AUX16: JP34.6, U17.P11
POCI_AUX17: JP36.6, U18.P11
POCI_AUX18: JP38.6, U19.P11
POCI_AUX19: JP40.6, U20.P11
POCI_AUX20: JP42.6, U21.P11
POCI_AUX21: JP44.6, U22.P11
POCI_AUX22: JP46.6, U23.P11
POCI_AUX23: JP48.6, U24.P11
SCL: J1.4, J2.4, JP1.3, R1.1, U1.P13
SCL1: J3.4, J4.4, JP2.3, R7.1, U2.P13
SCL2: J5.4, J6.4, JP5.3, R13.1, U3.P13
SCL3: J7.4, J8.4, JP7.3, R19.1, U4.P13
SCL4: J9.4, J10.4, JP9.3, R25.1, U5.P13
SCL5: J11.4, J12.4, JP11.3, R31.1, U6.P13
SCL6: J13.4, J14.4, JP13.3, R37.1, U7.P13
SCL7: J15.4, J16.4, JP15.3, R43.1, U8.P13
SCL8: J17.4, J18.4, JP17.3, R49.1, U9.P13
SCL9: J19.4, J20.4, JP19.3, R55.1, U10.P13
SCL10: J21.4, J22.4, JP21.3, R61.1, U11.P13
SCL11: J23.4, J24.4, JP23.3, R67.1, U12.P13
SCL12: J25.4, J26.4, JP25.3, R73.1, U13.P13
SCL13: J27.4, J28.4, JP27.3, R79.1, U14.P13
SCL14: J29.4, J30.4, JP29.3, R85.1, U15.P13
SCL15: J31.4, J32.4, JP31.3, R91.1, U16.P13
SCL16: J33.4, J34.4, JP33.3, R97.1, U17.P13
SCL17: J35.4, J36.4, JP35.3, R103.1, U18.P13
SCL18: J37.4, J38.4, JP37.3, R109.1, U19.P13
SCL19: J39.4, J40.4, JP39.3, R115.1, U20.P13
SCL20: J41.4, J42.4, JP41.3, R121.1, U21.P13
SCL21: J43.4, J44.4, JP43.3, R127.1, U22.P13
SCL22: J45.4, J46.4, JP45.3, R133.1, U23.P13
SCL23: J47.4, J48.4, JP47.3, R139.1, U24.P13
SCX: JP3.4, SCX.2, U1.P3
SCX1: JP4.4, SCX1.2, U2.P3
SCX2: JP6.4, SCX2.2, U3.P3
SCX3: JP8.4, SCX3.2, U4.P3
SCX4: JP10.4, SCX4.2, U5.P3
SCX5: JP12.4, SCX5.2, U6.P3
SCX6: JP14.4, SCX6.2, U7.P3
SCX7: JP16.4, SCX7.2, U8.P3
SCX8: JP18.4, SCX8.2, U9.P3
SCX9: JP20.4, SCX9.2, U10.P3
SCX10: JP22.4, SCX10.2, U11.P3
SCX11: JP24.4, SCX11.2, U12.P3
SCX12: JP26.4, SCX12.2, U13.P3
SCX13: JP28.4, SCX13.2, U14.P3
SCX14: JP30.4, SCX14.2, U15.P3
SCX15: JP32.4, SCX15.2, U16.P3
SCX16: JP34.4, SCX16.2, U17.P3
SCX17: JP36.4, SCX17.2, U18.P3
SCX18: JP38.4, SCX18.2, U19.P3
SCX19: JP40.4, SCX19.2, U20.P3
SCX20: JP42.4, SCX20.2, U21.P3
SCX21: JP44.4, SCX21.2, U22.P3
SCX22: JP46.4, SCX22.2, U23.P3
SCX23: JP48.4, SCX23.2, U24.P3
SDA/PICO: J1.3, J2.3, JP1.4, R2.1, U1.P14
SDA/PICO1: J3.3, J4.3, JP2.4, R8.1, U2.P14
SDA/PICO2: J5.3, J6.3, JP5.4, R14.1, U3.P14
SDA/PICO3: J7.3, J8.3, JP7.4, R20.1, U4.P14
SDA/PICO4: J9.3, J10.3, JP9.4, R26.1, U5.P14
SDA/PICO5: J11.3, J12.3, JP11.4, R32.1, U6.P14
SDA/PICO6: J13.3, J14.3, JP13.4, R38.1, U7.P14
SDA/PICO7: J15.3, J16.3, JP15.4, R44.1, U8.P14
SDA/PICO8: J17.3, J18.3, JP17.4, R50.1, U9.P14
SDA/PICO9: J19.3, J20.3, JP19.4, R56.1, U10.P14
SDA/PICO10: J21.3, J22.3, JP21.4, R62.1, U11.P14
SDA/PICO11: J23.3, J24.3, JP23.4, R68.1, U12.P14
SDA/PICO12: J25.3, J26.3, JP25.4, R74.1, U13.P14
SDA/PICO13: J27.3, J28.3, JP27.4, R80.1, U14.P14
SDA/PICO14: J29.3, J30.3, JP29.4, R86.1, U15.P14
SDA/PICO15: J31.3, J32.3, JP31.4, R92.1, U16.P14
SDA/PICO16: J33.3, J34.3, JP33.4, R98.1, U17.P14
SDA/PICO17: J35.3, J36.3, JP35.4, R104.1, U18.P14
SDA/PICO18: J37.3, J38.3, JP37.4, R110.1, U19.P14
SDA/PICO19: J39.3, J40.3, JP39.4, R116.1, U20.P14
SDA/PICO20: J41.3, J42.3, JP41.4, R122.1, U21.P14
SDA/PICO21: J43.3, J44.3, JP43.4, R128.1, U22.P14
SDA/PICO22: J45.3, J46.3, JP45.4, R134.1, U23.P14
SDA/PICO23: J47.3, J48.3, JP47.4, R140.1, U24.P14
